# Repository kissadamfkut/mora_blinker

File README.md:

Mora-blinker
========== 
## Goals
  
- Provide a simple and cheap educational embedded project
- Demonstrate basic electric design 
- Demonstrate both C++ basics and advanced tricks
- More entertaining first program than a 'Hello world'
- Educate for software design in low-end environments

## How to use

- The schematics and the PCB board can be found in the hw folder. You can open the files with KiCAD 6
- The software is in the sw folder. Do not forget to also pull the git submodules!
- The build environment for the software includes avr-gcc 11.2, avrdude 6.4 and make 4.3
- Do not connect the battery when using a 5V ISP!
- After building the PCB, connect an STK500 or similar, and type ```make program```
- You can switch animations with the reset button

## Bill of materials

- CR2032 holder
- CR2032
- 100 nF capacitor
- Yellow LEDs (x5)
- 120 ohm resistors (x5)
- 9.1 kohm resistor
- Button
- ATtiny13A

## Theory of operation

The timer overflow interrupt drives a soft-PWM routine. The running animation changes an array of the LEDs' duty cycles. Resetting the device, the content of the SRAM is not random, so the index of the last animation is known, except for the cold-start, when it is random (not a problem). Some data is stored in the EEPROM to save space.
   
## Known issues  
  
- Fuse calculation could be more describing
- May further optimize base code
- Less numeric constant

## Work of a student

## Full installion on Debian systems
```bash
sudo apt intsall gcc-avr avr-libc make avrdude
cd sw
make
make program
sudo apt install kdevelop #Optional
```

## Full installation on Windows systems (not tested)
- Install the lates AVR-GCC (for eg. https://blog.zakkemble.net/avr-gcc-builds/)
- Install Code::Blocks (https://www.codeblocks.org/)
- Open the project, and compile the elf file
- Use the driver of the programmer to deploy the code

## FAQ
Sometimes the programmers' device files are created with special permission on linux based systems. You should gather unix group membership to the proper group (dialout, uucp etc.), so you can program your device without sudo

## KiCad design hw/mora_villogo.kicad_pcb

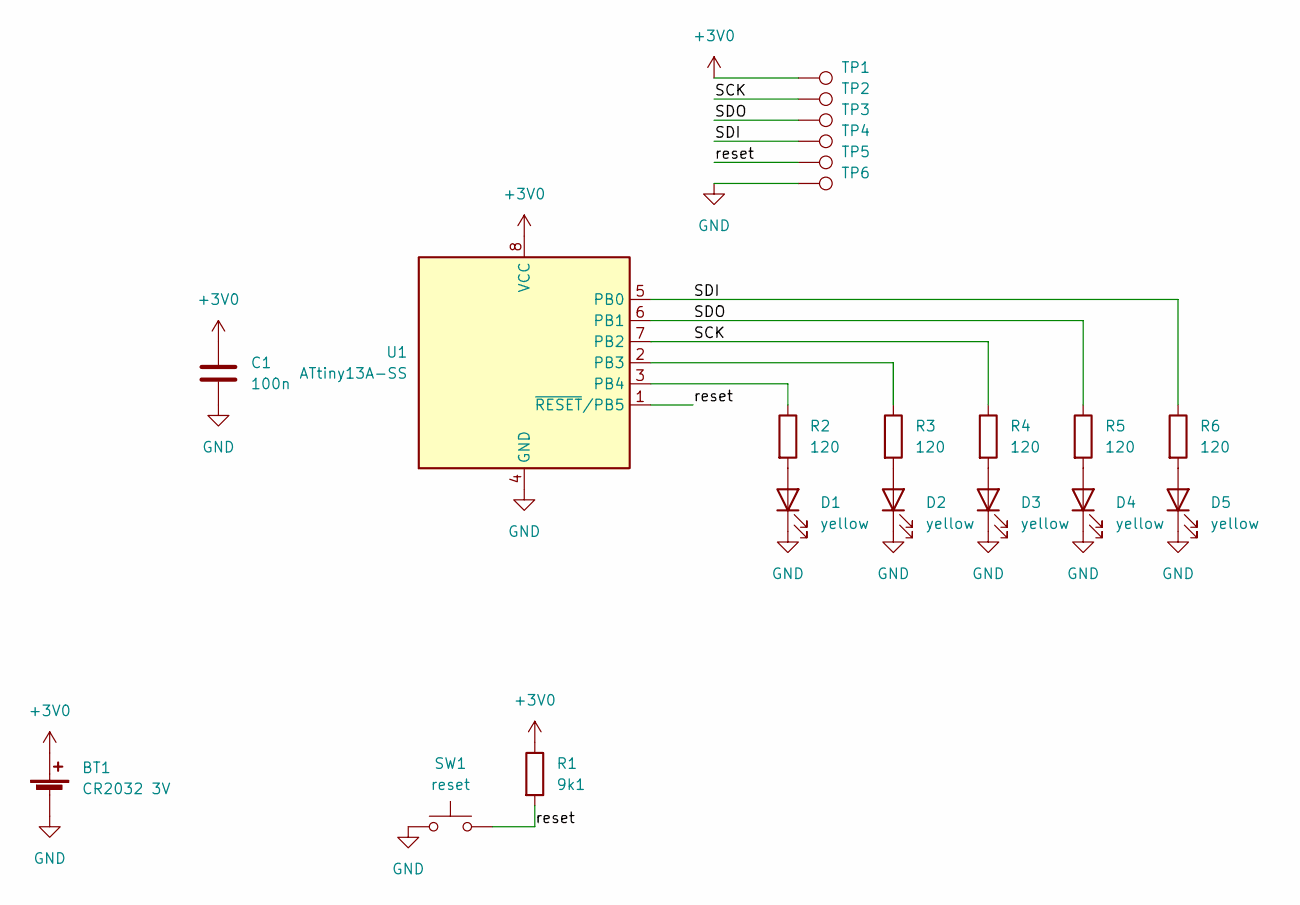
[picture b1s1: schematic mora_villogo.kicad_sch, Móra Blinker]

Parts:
BT1: CR2032 3V; BatteryHolder_ComfortableElectronic_CH273-2450_1x2450
C1: 100n; C_0805_2012Metric_Pad1.18x1.45mm_HandSolder
D1, D2, D3, D4, D5: yellow; LED_0805_2012Metric_Pad1.15x1.40mm_HandSolder
R1: 9k1; R_0805_2012Metric_Pad1.20x1.40mm_HandSolder
R2, R3, R4, R5, R6: 120; R_0805_2012Metric_Pad1.20x1.40mm_HandSolder
SW1: reset; SW_Push_1P1T_NO_6x6mm_H9.5mm
TP1, TP2, TP3, TP4, TP5, TP6: TestPoint; TestPoint_Pad_D3.0mm
U1: ATtiny13A-SS; SOIC-8_3.9x4.9mm_P1.27mm

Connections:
+3V0: BT1.1 (+), C1.1, R1.1, TP1.1, U1.8 (VCC)
/SCK: R4.1, TP2.1, U1.7 (PB2)
/SDI: R6.1, TP4.1, U1.5 (PB0)
/SDO: R5.1, TP3.1, U1.6 (PB1)
/reset: R1.2, SW1.2, TP5.1, U1.1 (~RESET/PB5)
GND: BT1.2 (-), C1.2, D1.1 (K), D2.1 (K), D3.1 (K), D4.1 (K), D5.1 (K), SW1.1, TP6.1, U1.4 (GND)
unnamed: D1.2 (A), R2.2
unnamed: D2.2 (A), R3.2
unnamed: D3.2 (A), R4.2
unnamed: D4.2 (A), R5.2
unnamed: D5.2 (A), R6.2
unnamed: R2.1, U1.3 (PB4)
unnamed: R3.1, U1.2 (PB3)

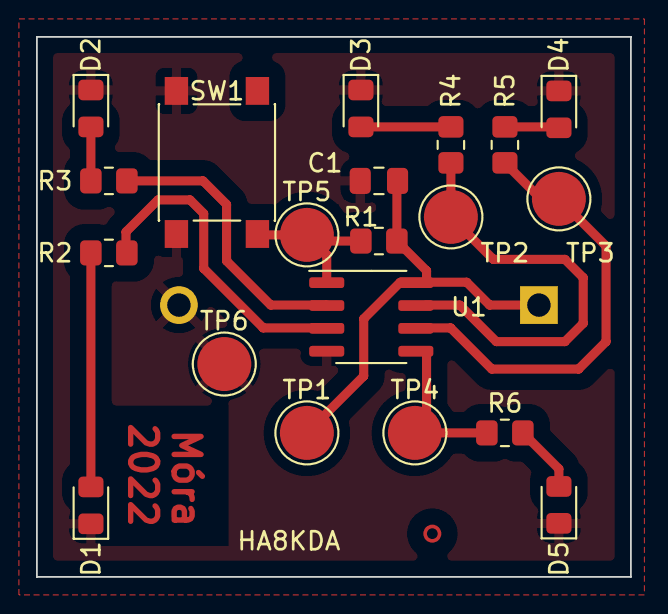
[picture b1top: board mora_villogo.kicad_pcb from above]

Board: 2 copper layers, 33.0 x 30.0 mm, 21 parts (1 on the bottom side), 13 nets.

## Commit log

2022-04-15 Add HW
2022-04-15 Add first software version
2022-04-17 Move animation pointres to the EEPROM. Over 17 animations it saves space
2022-04-17 Code format
2022-04-17 Remove unnecessary volatile qualifier, saving program memory (8 bytes).
2022-04-18 Fix register saving in the interrupt of timing.cpp
2022-04-18 Fix fade off in fade.cpp
2022-04-19 Add student animations
2022-04-19 Add metadata
2022-04-19 Reorder README sections
2023-01-06 Add Code::blocks project file
